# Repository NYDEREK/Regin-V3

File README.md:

# Regin-V3

Line follower na STM32G474 z 16 czujnikami analogowymi (multiplekser), mostkami BTN9970 i turbina na ESC.

Kod STM32 znajduje sie w:

`SOFTWARE/ReginV3_LFT_Code/Regin-V3-LFT-Code`

Najwazniejsze pliki:

- `Core/Src/Line_Follower.c` - jazda po linii i PID.
- `Core/Src/SimpleParser.c` - komendy Bluetooth z aplikacji.
- `Core/Inc/robot_config.h` - stale robota (PWM, ESC, bateria, Bluetooth).

## Konwencja czujnikow i PID

Firmware ma oryginalny uklad kierunkow (stan z commita `a179ecc`):

- pozycja linii liczona w `SensorRead()` w `Line_Follower.c`: 1000 to prawa krawedz listwy (`SensorArray[2]`), 16000 lewa (`SensorArray[13]`), srodek 8500.
- `error = 8500 - pozycja`: plus oznacza linie na prawo od srodka, wtedy lewy silnik przyspiesza i robot skreca w prawo.
- `Last_end`: 0 = linie ostatnio widzial prawy skrajny czujnik, 1 = lewy (z timerem ok. 2 ms).
- `sharp_turn()` (zgubiona linia): przy `Last_end = 1` prawy silnik dostaje `*_right`, lewy `*_left`, przy `Last_end = 0` odwrotnie.
- aplikacja odwraca kolejnosc czujnikow, wiec na wykresie slupek 1 jest po lewej stronie robota.

## Aplikacja Android

Wlasna aplikacja Regina jest w `SOFTWARE/Android App/ReginApp`, gotowy plik: `apk/REGIN-V3-debug.apk`. Ma zakladki `Drive` (turbina, PID, predkosci), `Sensors` (wszystkie 16 czujnikow jako slupki z wartosciami), `Joystick`, `Log` i `Settings`. Szczegoly w README aplikacji.

Firmware mowi tym samym protokolem co [GRUZIK4.0](https://github.com/NYDEREK/GRUZIK4.0), wiec dziala tez aplikacja z tamtego repo (`Android App/RobotApp`), ale pokazuje tylko 12 czujnikow i ma zakladki mapowania, ktorych Regin nie obsluguje. Modul Bluetooth to HC-04 na UART 9600.

Komendy:

- nastawy: `Kp`, `Kd`, `Treshold`, `Base_speed`, `Max_speed`, `Sharp_bend_speed_left/right`, `Bend_speed_left/right`, `Turbine_Speed`, `Turbine_Prep_Time`.
- start i stop: `StartNormal=1`, `Mode=Y`, `Mode=N`.
- joystick: `Manual=<lewy>,<prawy>`, robot staje po 350 ms bez pakietow.
- czyszczenie opon: `CleanSpeed=<pwm>`, `Clean=1`, `Clean=0`.
- czujniki: `Telemetry=debug` wysyla co 250 ms linie `DBG,<pozycja>,<aktywne>,<ostatni koniec>,<9 pol enkoderow/IMU = 0>,<S1>..<S16>` (S1 = prawa krawedz, S16 = lewa), `Telemetry=off` konczy.
- nazwa modulu: `BtNameNow=<nazwa>` (modul musi byc w trybie AT).

Regin nie ma enkoderow, IMU ani karty SD, wiec mapowanie i odometria (zakladki `Mapping` i `Odometry` w aplikacji GRUZIK4.0) nie dzialaja. Robot odpowiada wtedy bledem i nie rusza:

```text
MAP_ERROR,unsupported,no_odometry_sd
UPLOAD_ERROR,unsupported
TELEMETRY,odom_unsupported
BT_NAME_ERROR,no_sd_use_try_now
```

Uwagi:

- `Turbine_Speed` z aplikacji to 0..1000, czyli 1000..2000 us na ESC.
- `Turbine_Prep_Time` to czas w ms od wlaczenia turbiny do startu PID. Bez aplikacji domyslnie 1000 ms.
- Ponizej 11 V robot nie wystartuje (`! Low Battery !`).
- Telemetria `DBG` dziala tylko gdy robot stoi, bo wysylanie po UART blokuje odczyt czujnikow.

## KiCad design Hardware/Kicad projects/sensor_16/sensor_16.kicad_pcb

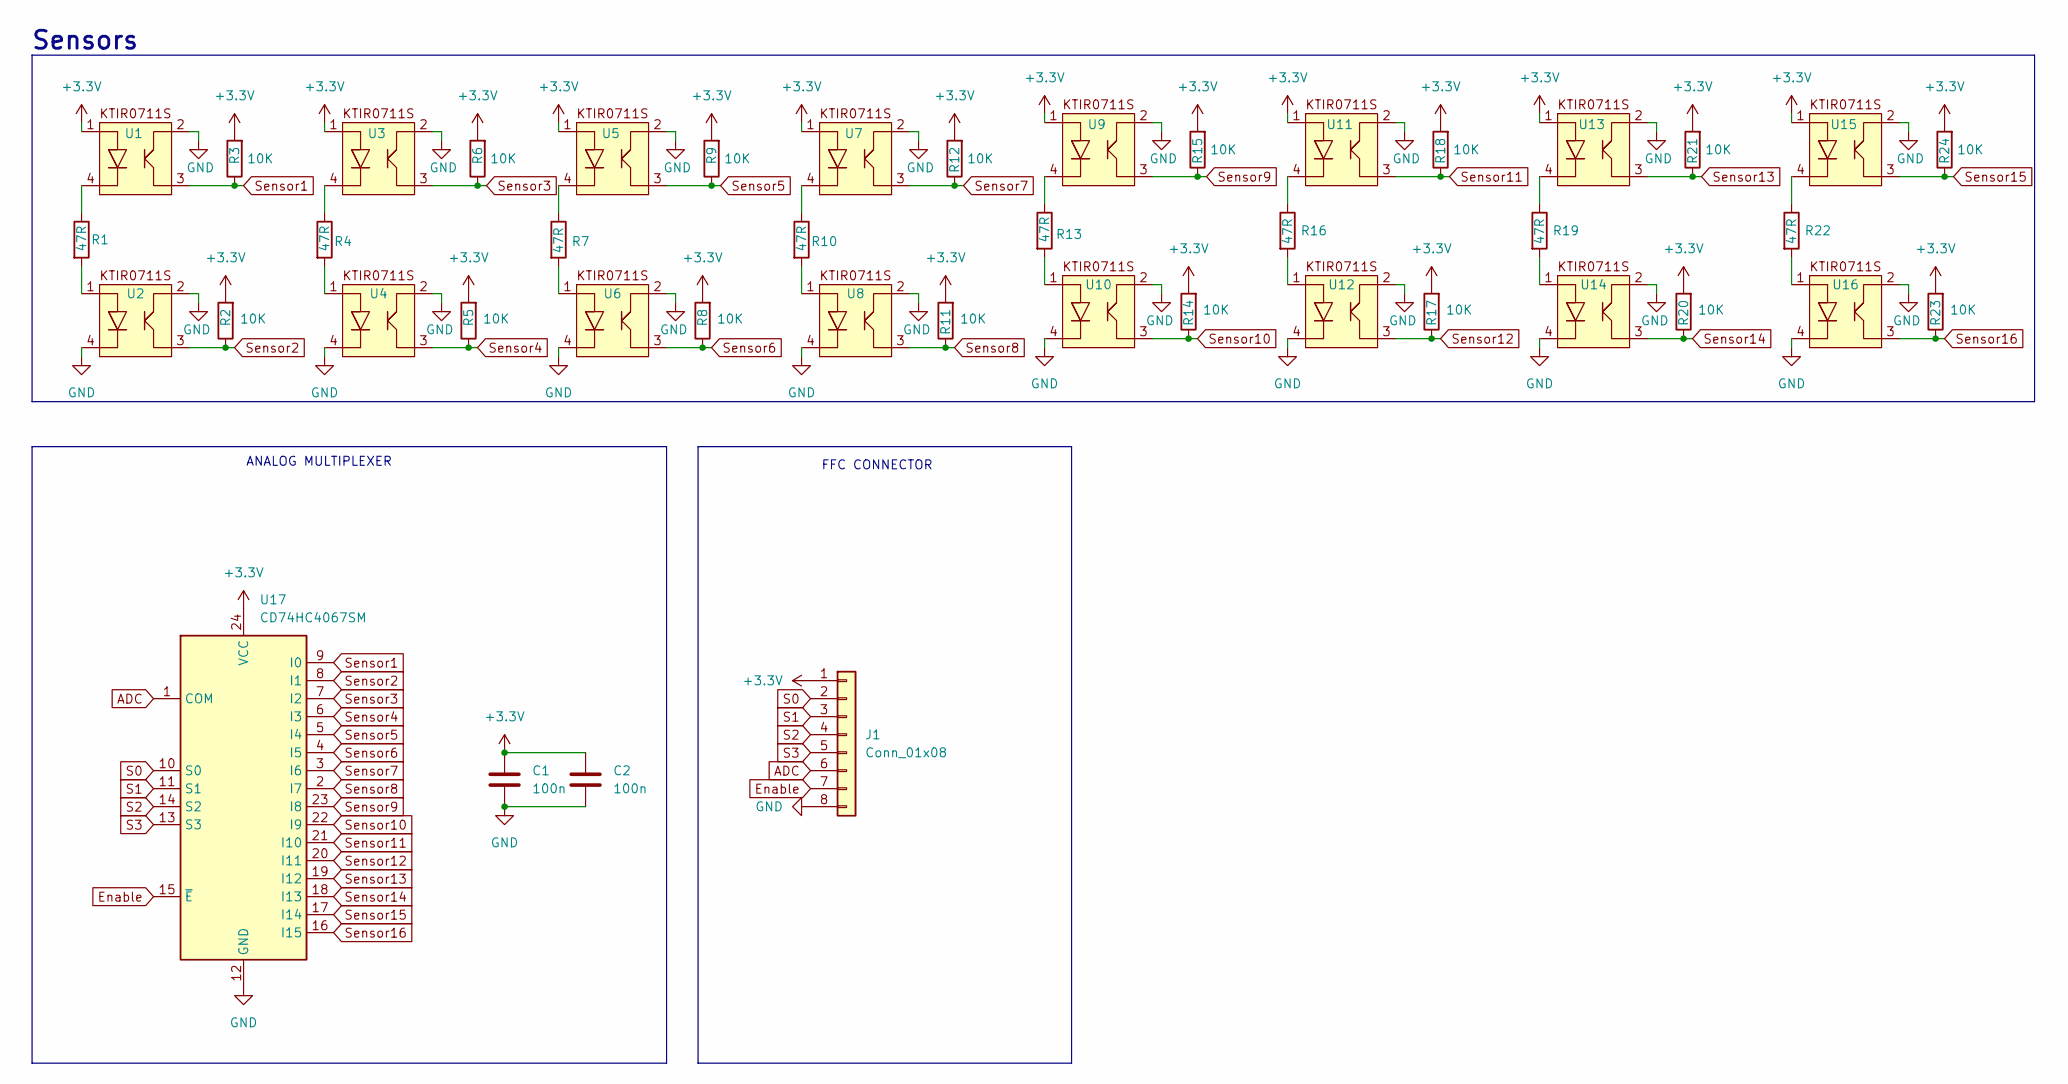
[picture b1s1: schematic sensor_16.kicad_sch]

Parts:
C1, C2: 100n; C_0402_1005Metric_Pad0.74x0.62mm_HandSolder
J1: Conn_01x08; Hirose_FH12-8S-0.5SH_1x08-1MP_P0.50mm_Horizontal
R1, R4, R7, R10, R13, R16, R19, R22: 47R; R_0603_1608Metric_Pad0.98x0.95mm_HandSolder
R2, R3, R5, R6, R8, R9, R11, R12, R14, R15, R17, R18, R20, R21, R23, R24: 10K; R_0402_1005Metric_Pad0.72x0.64mm_HandSolder
U1, U2, U3, U4, U5, U6, U7, U8, U9, U10, U11, U12, U13, U14, U15, U16: KTIR0711S
U17: CD74HC4067SM; TSSOP24_4P5X7P9_TEX-M

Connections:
+3.3V: C1.1, C2.1, J1.1, R2.2, R3.2, R5.2, R6.2, R8.2, R9.2, R11.2, R12.2, R14.2, R15.2, R17.2, R18.2, R20.2, R21.2, R23.2, R24.2, U1.1, U3.1, U5.1, U7.1, U9.1, U11.1, U13.1, U15.1, U17.24 (VCC)
ADC: J1.6, U17.1 (COM)
Enable: J1.7, U17.15 (~E)
GND: C1.2, C2.2, J1.8, U1.2, U2.2, U2.4, U3.2, U4.2, U4.4, U5.2, U6.2, U6.4, U7.2, U8.2, U8.4, U9.2, U10.2, U10.4, U11.2, U12.2, U12.4, U13.2, U14.2, U14.4, U15.2, U16.2, U16.4, U17.12 (GND)
unnamed: R1.1, U1.4
unnamed: R1.2, U2.1
unnamed: R4.1, U3.4
unnamed: R4.2, U4.1
unnamed: R7.1, U5.4
unnamed: R7.2, U6.1
unnamed: R10.1, U7.4
unnamed: R10.2, U8.1
unnamed: R13.1, U9.4
unnamed: R13.2, U10.1
unnamed: R16.1, U11.4
unnamed: R16.2, U12.1
unnamed: R19.1, U13.4
unnamed: R19.2, U14.1
unnamed: R22.1, U15.4
unnamed: R22.2, U16.1
S0: J1.2, U17.10 (S0)
S1: J1.3, U17.11 (S1)
S2: J1.4, U17.14 (S2)
S3: J1.5, U17.13 (S3)
Sensor1: R3.1, U1.3, U17.9 (I0)
Sensor2: R2.1, U2.3, U17.8 (I1)
Sensor3: R6.1, U3.3, U17.7 (I2)
Sensor4: R5.1, U4.3, U17.6 (I3)
Sensor5: R9.1, U5.3, U17.5 (I4)
Sensor6: R8.1, U6.3, U17.4 (I5)
Sensor7: R12.1, U7.3, U17.3 (I6)
Sensor8: R11.1, U8.3, U17.2 (I7)
Sensor9: R15.1, U9.3, U17.23 (I8)
Sensor10: R14.1, U10.3, U17.22 (I9)
Sensor11: R18.1, U11.3, U17.21 (I10)
Sensor12: R17.1, U12.3, U17.20 (I11)
Sensor13: R21.1, U13.3, U17.19 (I12)
Sensor14: R20.1, U14.3, U17.18 (I13)
Sensor15: R24.1, U15.3, U17.17 (I14)
Sensor16: R23.1, U16.3, U17.16 (I15)

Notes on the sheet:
FFC CONNECTOR
Sensors
ANALOG MULTIPLEXER

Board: 2 copper layers, 44 parts (16 on the bottom side), 40 nets, no tracks yet.

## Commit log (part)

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2025-10-27 v1 schemat
    faefesgges
2026-03-16 fefewfe
    fefef
